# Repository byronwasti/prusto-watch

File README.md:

*WIP*
*Note: I've recently picked up the PineTime and am hoping to continue this project using that hardware when I find time.*

# Prusto Watch
An Open Source smart watch with firmware written in Rust. `src/` folder is fairly bare while proof-of-concept work is in various `examples/` folders.

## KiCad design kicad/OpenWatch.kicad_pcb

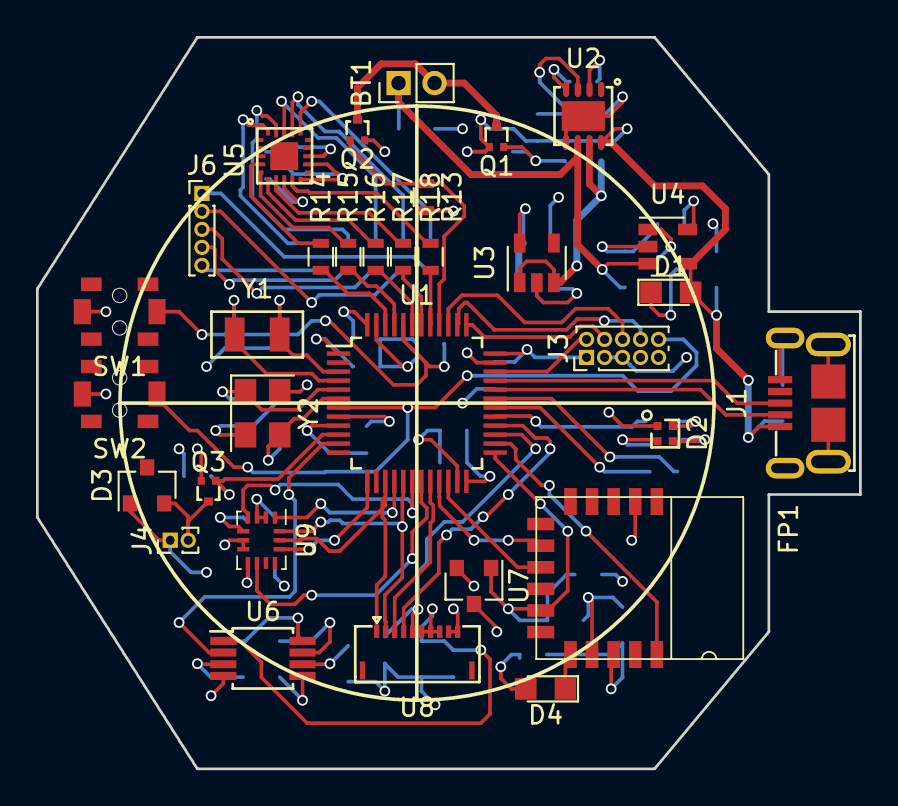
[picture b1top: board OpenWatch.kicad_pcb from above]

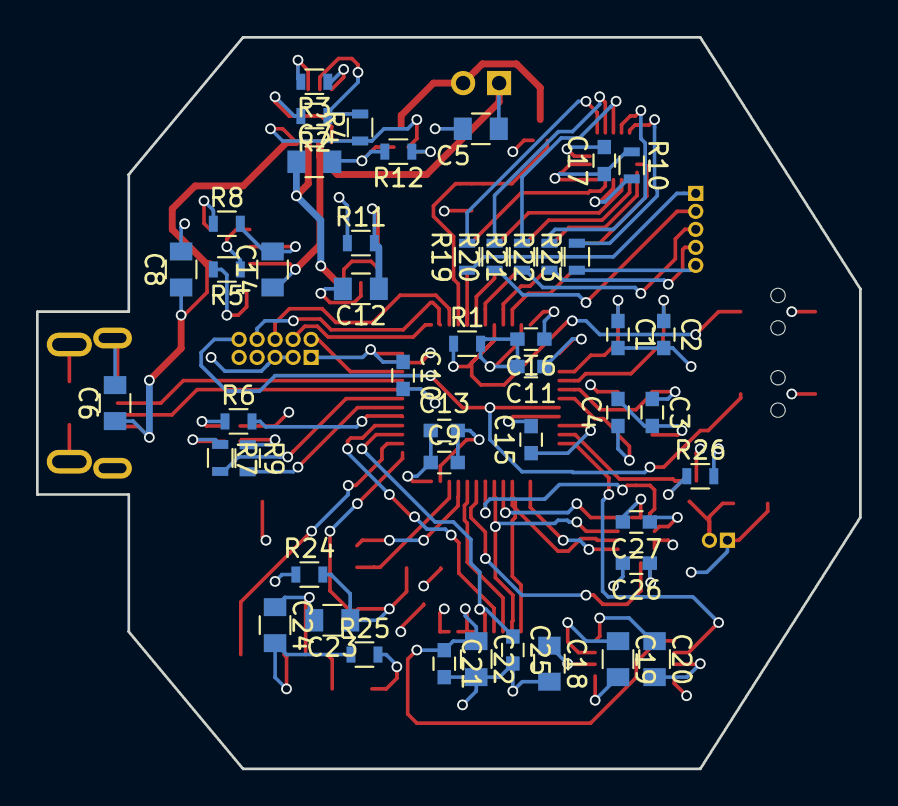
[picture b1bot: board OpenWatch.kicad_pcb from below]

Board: 4 copper layers, 45.7 x 40.6 mm, 79 parts (47 on the bottom side), 75 nets.

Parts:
BT1: Battery_Cell; Pin_Header_Straight_1x02_Pitch2.00mm
C1, C2: 12.5pF; C_0603
C3, C4: 18pF; C_0603
C5, C8, C14: 4.7uF; C_0805
C6, C24: 10uF; C_0805
C7, C18, C19, C20, C22, C23: 1uF; C_0805
C9, C10, C11, C13, C15, C16, C17, C21, C25, C26, C27: 100nF; C_0603
C12: 2.2uF; C_0805
D1, D4: LED; LED_0805
D2: LED_ARGB; SMLP34RGB2W3
D3: BAT54; SOT-23
FP1: BM71BLES1FC2
J1: USB_microB_2040002-1
J3: Conn_02x05_Odd_Even; Pin_Header_Straight_2x05_Pitch1.00mm
J4: Vibration Motor; Pin_Header_Straight_1x02_Pitch1.00mm
J6: Conn_01x05; Pin_Header_Straight_1x05_Pitch1.00mm
Q1, Q2, Q3: RUM002N02T2L; VMT3
R1, R8, R10, R14, R15, R16, R17, R18, R19, R20, R21, R22, R23: 10K; R_0603
R2, R12, R13, R26: 100K; R_0603
R3: 402; R_0603
R4: 200K; R_0603
R5: 470; R_0603
R6, R7, R9, R25: 1K; R_0603
R11: DNP-0; R_0603
R24: 4.75K; R_0603
SW1, SW2: SW_Push; PTS820_J15M_SMTR_LFS
U1: STM32F303RCT6-48; LQFP-48_7x7mm_Pitch0.5mm
U2: TPS2113ADRBR; SON-8
U3: TSP70933DBVR; SOT-23-5
U4: MCP73831T-2ACI; SOT-23-5
U5: AT42QT1070-MMHR
U6: TPS60241DGKR; MSOP-8_3x3mm_Pitch0.65mm
U7: RT9818A-18GV; SOT-23
U8: WM1389CT-ND; Molex_FPC_5034801000
U9: LSM6DSL; Bosch_LGA-14_3x2.5mm_Pitch0.5mm
Y1: ECS.327; ECX-31B
Y2: FA-238; Crystal_SMD_SeikoEpson_FA238V-4pin_3.2x2.5mm

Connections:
+3V3: C9.1, C10.1, C11.1, C13.1, C15.1, C16.1, C17.1, C18.1, C24.2, C26.1, C27.1, D2.1, D3.1, FP1.14, J3.1, J4.1, R10.1, R11.1, R24.1, R25.1, SW1.1, U1.1, U1.9, U1.24, U1.36, U1.48, U5.9, U5.11, U6.6, U7.3, U9.5, U9.8
+5V: C21.1, C22.1, U6.1, U8.6, U8.7, U8.8
/5V_EN: U1.11, U6.2
/BATT_EN: Q2.1, R13.1, U1.40
/BLE_CONF: FP1.16, U1.26
/BLE_nRST: C23.1, FP1.10, R24.2, U1.25, U7.1
/DISP_EN: C25.1, U1.27, U8.5
/DISP_SCLK: U1.15, U8.1, U9.13
/DISP_SCS: U1.20, U8.3
/DISP_SDI: U1.17, U8.2, U9.14
/D_N: J1.2, U1.32
/D_P: J1.3, U1.33
/EXTCOMIN: U1.28, U8.4
/IMU_CS: U1.13, U9.12
/IMU_INT_1: U1.18, U9.4
/IMU_INT_2: U1.19, U9.9
/IMU_SDO: U1.16, U9.1
/KEY_0: J6.1, R19.1
/KEY_1: J6.2, R20.1
/KEY_2: J6.3, R21.1
/KEY_3: J6.4, R22.1
/KEY_4: J6.5, R23.1
/LED_BLUE: R7.2, U1.31
/LED_GREEN: R9.2, U1.30
/LED_RED: R6.2, U1.29
/MOTOR_EN: Q3.1, R26.1, U1.10
/NRST_TOUCH: R10.2, U5.13
/RX_BLE: FP1.7, U1.21
/STM_NRST: J3.10, SW2.2, U1.7
/TCK: J3.4, U1.37
/TDI: J3.8, U1.38
/TDO: J3.6, U1.39
/TMS: J3.2, U1.34
/TOUCH_0: R18.1, U1.41
/TOUCH_1: R14.1, U1.46
/TOUCH_2: R15.1, U1.45
/TOUCH_3: R16.1, U1.43
/TOUCH_4: R17.1, U1.42
/TX_BLE: FP1.8, U1.22
/VBATT: BT1.1, C5.1, C14.1, U2.6, U4.3
/VUSB: C6.1, C8.1, D1.2, J1.1, Q1.1, R4.1, R12.1, U2.8, U4.4
GND: C1.2, C2.2, C3.2, C4.2, C5.2, C6.2, C7.2, C8.2, C9.2, C10.2, C11.2, C12.2, C13.2, C14.2, C15.2, C16.2, C17.2, C18.2, C21.2, C22.2, C23.2, C24.1, C25.2, C26.2, C27.2, FP1.2, FP1.13, J1.5, J1.6, J1.7, J1.8, J1.9, J1.10, J1.11, J3.3, J3.5, Q1.2, Q2.2, Q3.2, R1.2, R2.2, R3.2, R8.2, R12.2, R13.2, R26.2, SW2.1, U1.8, U1.23, U1.35, U1.47, U2.2, U2.5, U3.2, U4.2, U5.8, U6.4, U7.2, U8.9, U8.10, U9.2, U9.3, U9.6, U9.7, Y2.2, Y2.4
unnamed: BT1.2, Q1.3, Q2.3
unnamed: C1.1, U1.3, Y1.2
unnamed: C2.1, U1.4, Y1.1
unnamed: C3.1, U1.5, Y2.1
unnamed: C4.1, U1.6, Y2.3
unnamed: C7.1, U2.7, U3.1, U3.3
unnamed: C12.1, R11.2, U3.5
unnamed: C19.1, U6.7
unnamed: C19.2, U6.5
unnamed: C20.1, U6.8
unnamed: C20.2, U6.3
unnamed: D1.1, R5.2
unnamed: D2.2, R6.1
unnamed: D2.3, R7.1
unnamed: D2.4, R9.1
unnamed: D3.2, J4.2, Q3.3
unnamed: D4.1, FP1.12
unnamed: D4.2, R25.2
unnamed: R1.1, SW1.2, U1.44
unnamed: R2.1, R4.2, U2.3
unnamed: R3.1, U2.4
unnamed: R5.1, U4.1
unnamed: R8.1, U4.5
unnamed: R14.2, U5.17
unnamed: R15.2, U5.16
unnamed: R16.2, U5.15
unnamed: R17.2, U5.14
unnamed: R18.2, U5.12
unnamed: R19.2, U5.5
unnamed: R20.2, U5.4
unnamed: R21.2, U5.3
unnamed: R22.2, U5.2
unnamed: R23.2, U5.1

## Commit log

2017-10-30 Adding inital files
2017-10-30 Adds links to additional components
2017-10-30 Adds initial library files and formatting
2017-10-30 Adds spec for IMU
2017-10-30 Added LSM6DSL KiPart file
2017-10-31 Adds LSM6DSL to library
2017-10-31 Adds microusb connector
2017-11-02 Basic schematic layout
2017-11-02 Adds bq24232 kipart csv
2017-11-02 Adds bq24232 part to open_watch lib
2017-11-02 Adds power management IC configuration
2017-11-02 Stops tracking of *-rescue.lib
2017-11-02 Fixes schematic to 4.07 KICAD
2017-11-04 Adds additional components to BOM
2017-11-04 Organizes BOM
2017-11-04 Finalizes certain schematic elements
2017-11-05 Finishes first implementation of the schematic
2017-11-05 Adds crystals and fixes minor schematic issues
2017-11-05 Replaces certain components in the BOM and removes unused parts
2017-11-05 Fixes some schematic issues and adds a 3-color LED
2017-11-05 Fixes a feedback issue
2017-11-06 Adding spec for battery holder
2017-11-06 Updates information about various things. Adds power budget
2017-11-06 Adds schematic PDF
2017-11-06 Fixes pull-up issues with JTAG wiring
2017-11-06 Fixes math in power budget
2017-11-06 Adds ability to reset BLE module using our MCU
2017-11-08 Associating most of the footprints.
2017-11-11 Adds additional footprint associations
2017-11-11 Adds ECX-31B footprint
2017-11-11 Add ARGB LED footprint SMLP34RGB2W3
2017-11-11 Fixes battery holder footprint
2017-11-11 Add VMT3 package for FET
2017-11-11 Associates more footprints
2017-11-12 Add SON-8 package
2017-11-12 Associate TPS602041 part with footprint
2017-11-12 Associated footprint for MCP73831
2017-11-12 Adds AT42QT1070 footprint
2017-11-12 Adds footprint associations
2017-11-12 Add Molex FPC 5034801000 footprint
2017-11-12 Associates all footprints
2017-11-13 Fix connections to display
2017-11-14 Fix various connection issues
2017-11-14 Change battery and battery connector to a much slimmer profile
2017-11-15 Add battery molex connector footprint
2017-11-15 Fix no pull down on transistor gates
2017-11-16 Change battery connector to two holes
2017-11-16 Initial placement of critical components
2017-11-16 Second iteration of placement
2017-11-16 Spread out components
2017-11-16 Add all components to be routed to PCB
2017-11-16 Add majority of routing
2017-11-17 Finish majority of routing
2017-11-17 Finish PCB routing
2017-12-04 Add basic blinky firmware
2017-12-07 Remove commented out code
2017-12-10 Disable semi-hosting for programming to flash
2017-12-10 Use self-generated STM32f303 crate
2017-12-12 Fix code to compile RTFM!
2017-12-12 Implement basic blinky {note: untested}
2017-12-14 Add RTFM based firmware for interrupt driven blinky
2018-01-30 Begin reorg
2018-01-31 Reorganize for a separate kicad and firmware repo
2018-01-31 Update cargo
2018-01-31 Update dependancies to allow for compiling without panicing rustc
2018-02-02 Implement basic blinky with RTFM V0.3
2018-02-02 Use embedded-hal for register manipulation
2018-02-06 Implement Basic Spi
2018-02-13 Add nb dependency
2018-02-13 Add example code
2018-02-13 Add spi usage example
2018-03-05 Add semihosting support
2018-03-05 Refactor to use BLE driver
2018-03-24 Adding examples
2018-03-26 Add echo BLE driver
2018-03-26 Basic display functional
2018-03-26 Update examples
2018-03-27 Implement some basic demos of LCD functionality
2018-05-03 Add various files
2018-05-03 Update names of various examples
2018-05-13 Various example updates
2018-05-14 Basic demo functionality
2018-05-14 Get demo ready
2018-08-21 Final update
